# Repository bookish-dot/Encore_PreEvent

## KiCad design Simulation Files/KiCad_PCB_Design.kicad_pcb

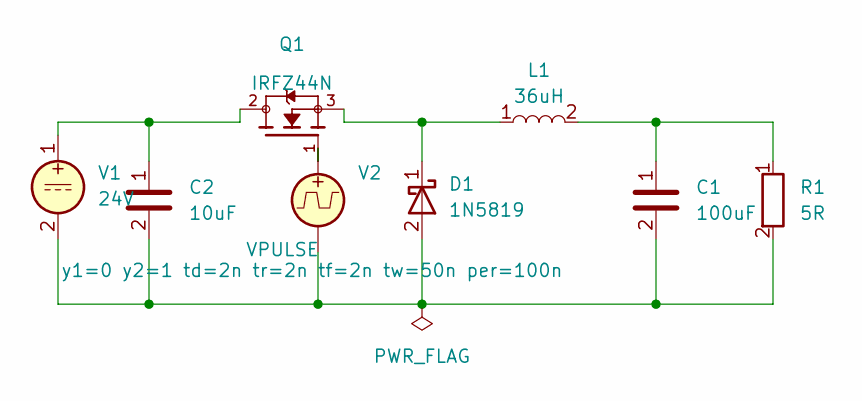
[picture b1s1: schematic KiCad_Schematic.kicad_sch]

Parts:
C1: 100uF; C_Radial_D4.0mm_H7.0mm_P1.50mm
C2: 10uF; C_Radial_D4.0mm_H5.0mm_P1.50mm
D1: 1N5819; D_DO-41_SOD81_P10.16mm_Horizontal
L1: 36uH; L_Radial_D12.0mm_P5.00mm_Fastron_11P
Q1: IRFZ44N; TO-3P-3_Vertical; PARTREV 09/21/10
R1: 5R; R_Axial_DIN0204_L3.6mm_D1.6mm_P5.08mm_Horizontal
V1: 24V; TerminalBlock_Phoenix_MPT-0,5-2-2.54_1x02_P2.54mm_Horizontal
V2: VPULSE; DIP-8_W7.62mm

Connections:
unnamed: C1.1, L1.2, R1.1
unnamed: C2.1, Q1.2, V1.1
unnamed: C1.2, C2.2, D1.2 (A), R1.2, V1.2, V2.2
unnamed: D1.1 (K), L1.1, Q1.3
unnamed: Q1.1, V2.1

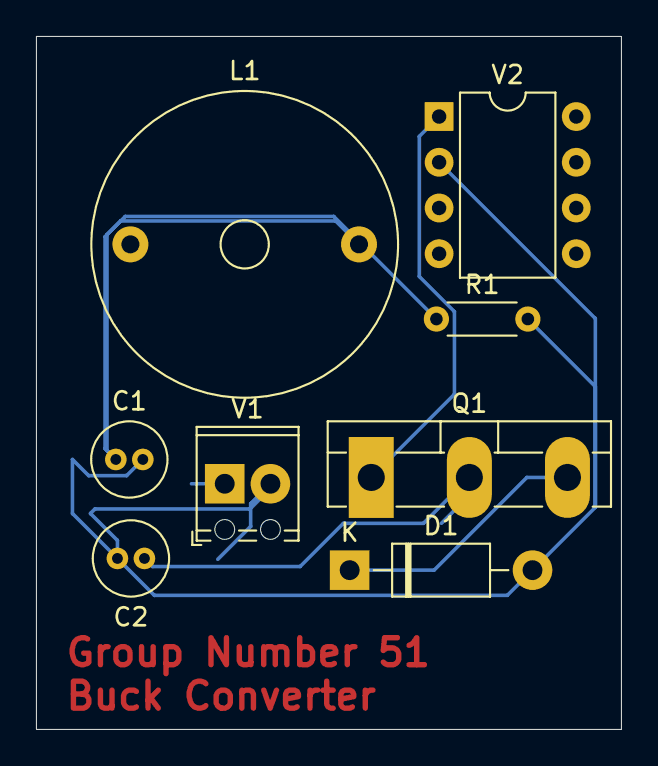
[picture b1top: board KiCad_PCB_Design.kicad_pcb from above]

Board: 2 copper layers, 32.5 x 38.5 mm, 8 parts (0 on the bottom side), 5 nets.
